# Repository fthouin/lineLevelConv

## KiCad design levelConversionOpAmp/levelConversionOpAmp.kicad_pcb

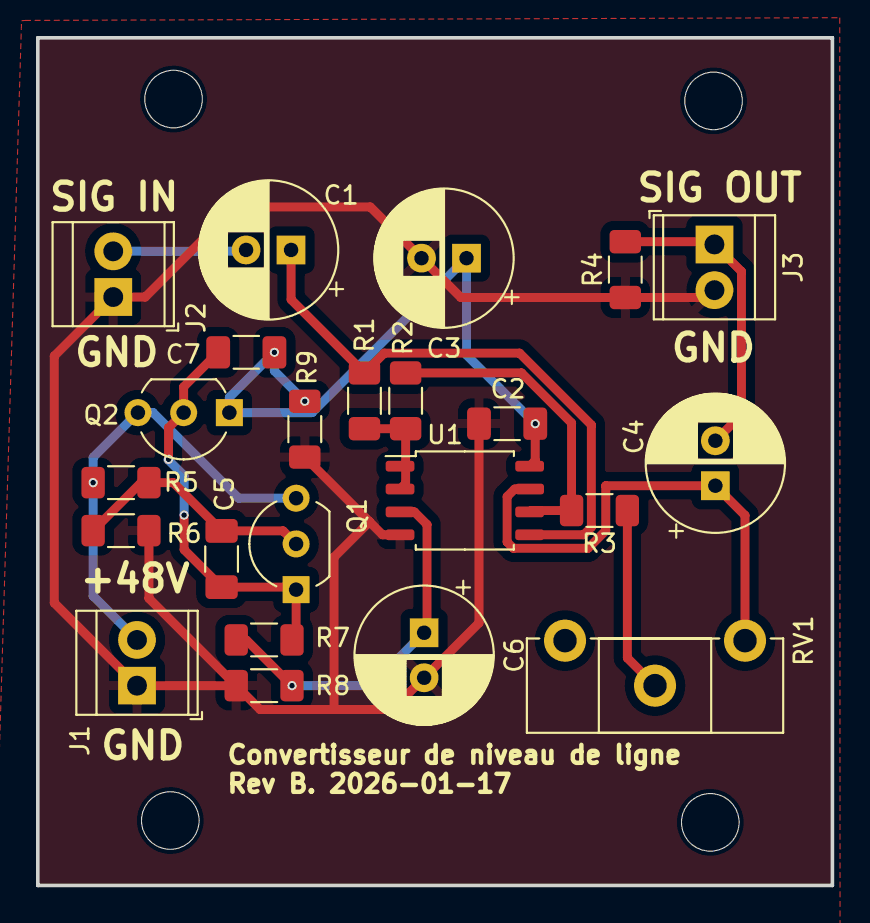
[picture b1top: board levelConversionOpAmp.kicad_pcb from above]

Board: 2 copper layers, 44.1 x 47.1 mm, 27 parts (0 on the bottom side), 13 nets.

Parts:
C1, C3, C4, C6: 47u/50V; CP_Radial_D7.5mm_P2.50mm
C2, C5, C7: 1u; C_1206_3216Metric_Pad1.33x1.80mm_HandSolder
J1: POW; TerminalBlock_TE_282834-2_1x02_P2.54mm_Horizontal
J2: IN; TerminalBlock_TE_282834-2_1x02_P2.54mm_Horizontal
J3: OUT; TerminalBlock_TE_282834-2_1x02_P2.54mm_Horizontal
Q1, Q2: PN2222A; TO-92_Inline_Wide
R1: 100k; R_1206_3216Metric_Pad1.30x1.75mm_HandSolder
R2, R5, R6, R7, R8, R9: 10k; R_1206_3216Metric_Pad1.30x1.75mm_HandSolder
R3: 1k; R_1206_3216Metric_Pad1.30x1.75mm_HandSolder
R4: 4k7; R_1206_3216Metric_Pad1.30x1.75mm_HandSolder
REF1, REF1#2, REF1#3, REF1#4: MountingHole_3.2mm_M3_DIN965
RV1: 10k; Potentiometer_ACP_CA14-H2,5_Horizontal
U1: TL082; SOIC-8_5.23x5.23mm_P1.27mm

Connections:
+48V: J1.2, Q1.3 (C), Q2.3 (C), R5.1
GND: C2.2, C3.2, C6.2, J1.1, J2.1, J3.2, R4.1, R6.2, R8.2, R9.2, U1.4 (V-)
unnamed: C4.1, RV1.1, U1.7
unnamed: C5.2, Q1.2 (B), R5.2, R6.1
unnamed: C5.1, C7.2, Q1.1 (E), Q2.2 (B), R7.1
unnamed: R3.1, RV1.2
unnamed: C6.1, R7.2, R8.1, U1.3 (+)
unnamed: C1.1, R1.2, U1.5 (+)
unnamed: R2.1, R3.2, U1.6 (-)
SIGIN: C1.2, J2.2
SIGOUT: C4.2, J3.1, R4.2
V+: C2.1, C3.1, C7.1, Q2.1 (E), R9.1, U1.8 (V+)
VREF: R1.1, R2.2, U1.1, U1.2 (-)

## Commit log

2023-05-12 Rev. A. Schema et tests sur breadboard
2023-06-08 Placement des composantes sur plaque perforee
2023-06-17 Changed layout a little. Added ground bias resistor at output to quickly set output DC level even when plugged into a high impedance load
2026-01-17 Made PCB with surface mount and correct cap tolerances
2026-01-17 Fab files
